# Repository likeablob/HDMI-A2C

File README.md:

# HDMI-A2C
A simple `HDMI Type A Male` to `mini HDMI (aka HDMI Type C) Male` adapter board.

## BOM
| Name                         | Quantity | Typ. price (USD) | Notes                                    |
| ---------------------------- | :------: | ---------------- | ---------------------------------------- |
| HDMI (Type A) Male Plug      |    1     | 0.2 ~ 0.9        | [See below](#hdmi-type-a-male-plug)      |
| mini HDMI (Type C) Male Plug |    1     | 0.3 ~ 1.8        | [See below](#mini-hdmi-type-c-male-plug) |

#### `HDMI (Type A) Male Plug`
- Notes
  - Before soldering, pins on the upper side must be bended slightly, to make the parts "grab" the board of 1 mm thickness. (It expects 1.6 mm of board thickness, however the mini HDMI plug requires 1 mm.)
  
- Data sheets
  -  ([src](https://www.aliexpress.com/item/32963116074.html))
- Sellers
  - Note that the following parts are not the same model exactly, however they are pin-compatible AFAIK.
  - [aitendo HDP19-017](https://www.aitendo.com/product/19008)
  - [Aliexpress 10PCS HDMI Male Jack/plug connector 19PIN 19P 1.6MM 180 Degree Gold-Plated hd 19 PIN](https://www.aliexpress.com/item/32963116074.html)

#### `mini HDMI (Type C) Male Plug`
- Data sheets
  -  ([src](https://www.aliexpress.com/item/32653409668.html))
  - [MH-02PLG.pdf](http://aitendo3.sakura.ne.jp/aitendo_data/product_img/cn/hdmi/MH-02PLG/MH-02PLG.pdf)
- Sellers
  - Note that the following parts are not the same model exactly, however they are pin-compatible AFAIK.
  - [aitendo MH-02PLG](https://www.aitendo.com/product/19500)
  - [Aliexpress cltgxdd Gold plating 19 PiN male plug C Type HDMI Jack Splint Type,HDMI repair replacement](https://www.aliexpress.com/item/32863394130.html)

## PCB
- Required specs
  - **PCB Thickness: 1mm**
    - This is required for the mini HDMI plug.
  - Layers: 2
  - PCB & Silkscreen color: Black and white, but choose anything you like.
- Gerber
  - See zip files under [./gerber](./gerber).
  - [`hdmi_a2c_rev1_panelized_3x4.zip`](./gerber/hdmi_a2c_rev1_panelized_3x4.zip) is a panelized one.
    - Credit: It was made with [This is Not Rocket Science]'s Gerber Panelizer.
  - Or just use KiCad v5 to generate files.
- For reference, I ordered the REV.1 board from JLCPCB in this time.

## Changelog
- REV.1
  - Initial release
  - Known issues:
    - `HDMI_A_HDP19-017_Horizontal.kicad_mod`: Though it's solderble, its pad pitch is a little narrower than the actual (0.5 mm).

## License
MIT

## Related projects
- ~~LandscaPi~~ TBD

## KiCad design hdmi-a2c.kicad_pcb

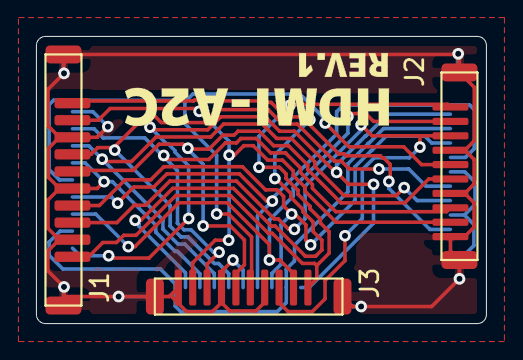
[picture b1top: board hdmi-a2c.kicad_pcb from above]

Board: 2 copper layers, 25.0 x 16.0 mm, 3 parts (0 on the bottom side), 15 nets.

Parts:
J1: HDMI_A; HDMI_A_HDP19-017_Horizontal
J2, J3: HDMI_C_1.3; HDMI_C_MH-02PLG_Horizontal

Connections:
GND: J1.2, J1.5, J1.8, J1.11, J1.17, J1.SH, J2.1, J2.4, J2.7, J2.10, J2.13, J2.SH, J3.1, J3.4, J3.7, J3.10, J3.13, J3.SH
HDMI_+5V: J1.18, J2.18, J3.18
HDMI_CEC: J1.13, J2.14, J3.14
HDMI_CK+: J1.10, J2.11, J3.11
HDMI_CK-: J1.12, J2.12, J3.12
HDMI_D0+: J1.7, J2.8, J3.8
HDMI_D0-: J1.9, J2.9, J3.9
HDMI_D1+: J1.4, J2.5, J3.5
HDMI_D1-: J1.6, J2.6, J3.6
HDMI_D2+: J1.1, J2.2, J3.2
HDMI_D2-: J1.3, J2.3, J3.3
HDMI_HPD: J1.19, J2.19, J3.19
HDMI_SCL: J1.15, J2.15, J3.15
HDMI_SDA: J1.16, J2.16, J3.16
HDMI_UTILITY: J1.14, J2.17, J3.17

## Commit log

2021-12-30 Add files
2021-12-30 Create LICENSE
